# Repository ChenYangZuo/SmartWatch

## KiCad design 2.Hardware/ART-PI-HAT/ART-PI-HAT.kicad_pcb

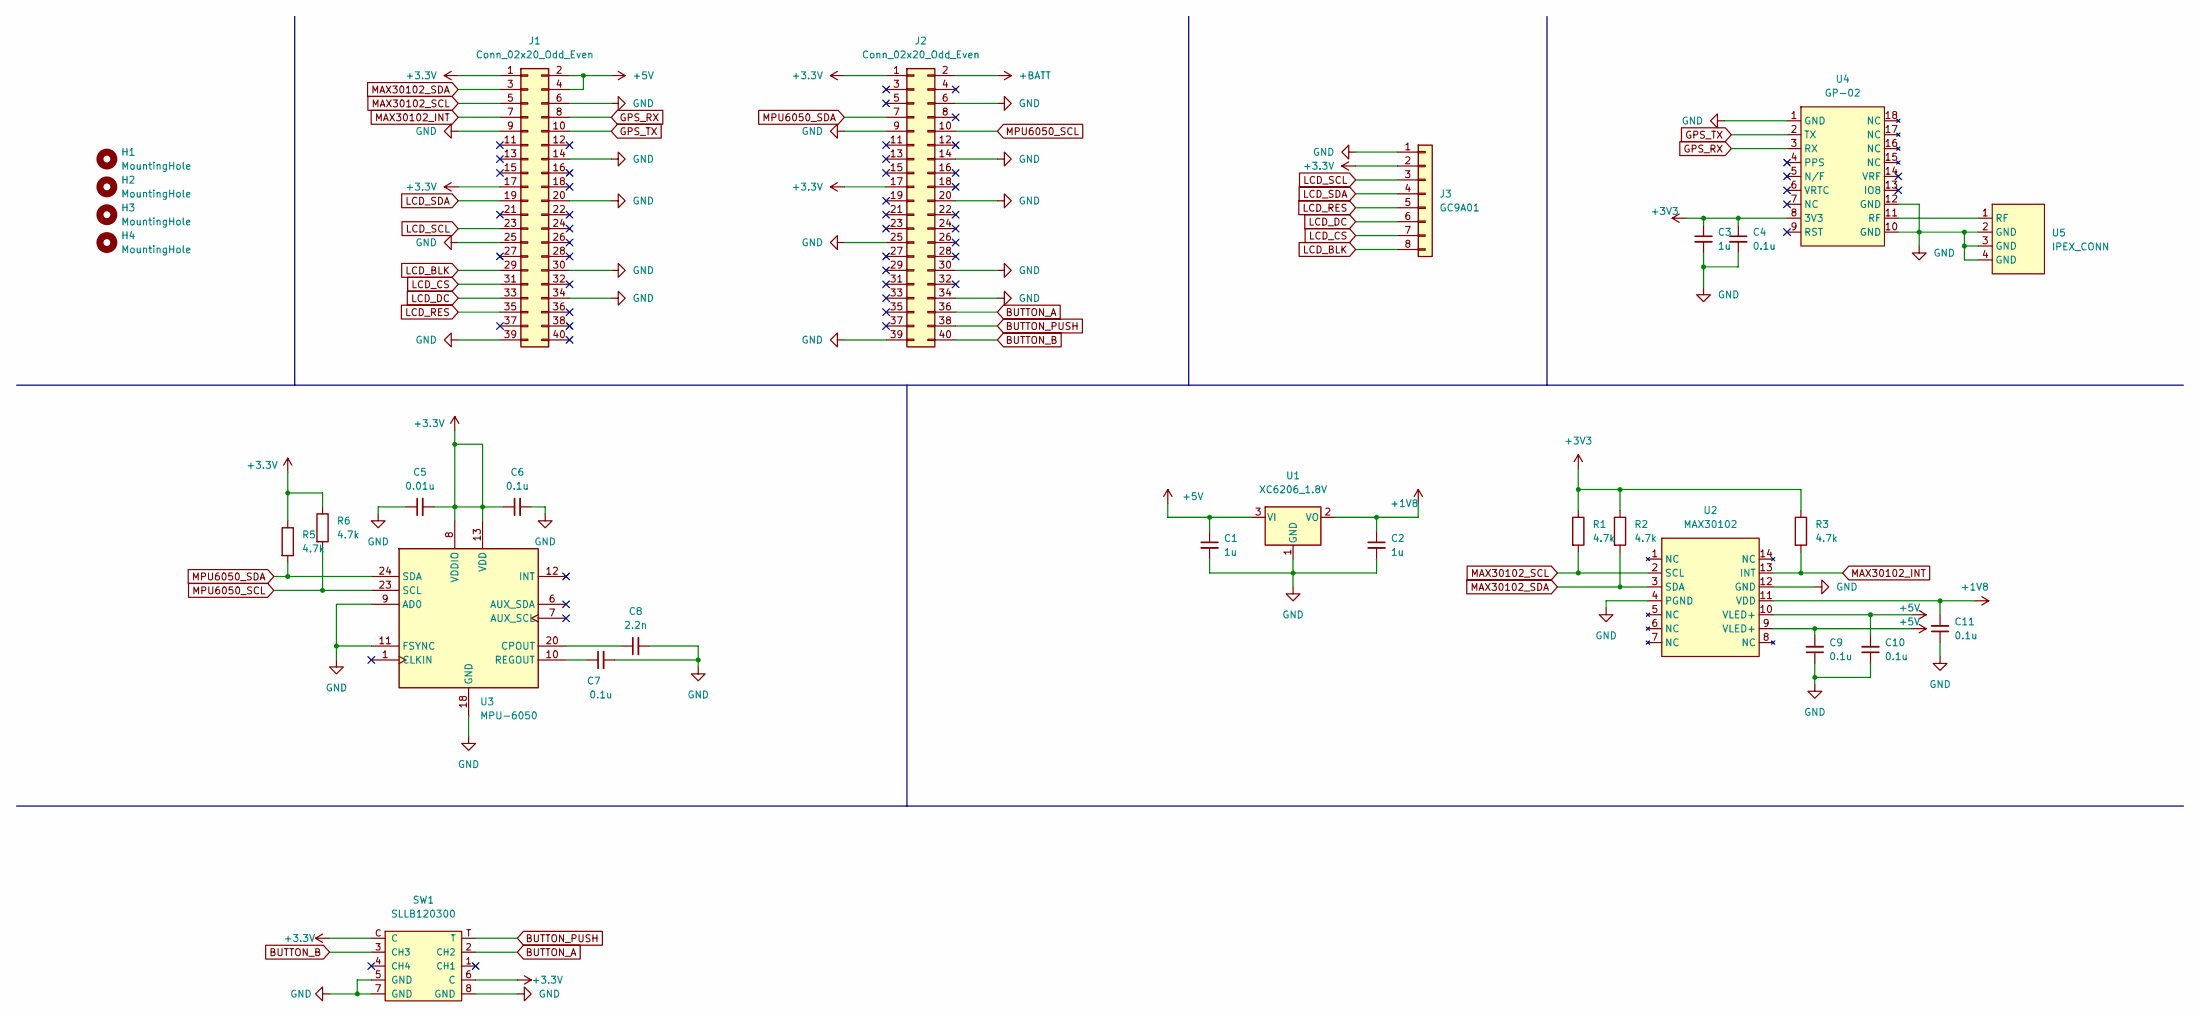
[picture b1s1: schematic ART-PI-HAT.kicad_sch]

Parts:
C1, C2, C3: 1u; C_0603_1608Metric
C4, C6, C7, C9, C10, C11: 0.1u; C_0603_1608Metric
C5: 0.01u; C_0603_1608Metric
C8: 2.2n; C_0603_1608Metric
H1, H2, H3, H4: MountingHole; TH_RASP_HAT
J1, J2: Conn_02x20_Odd_Even; PinHeader_2x20_P2.54mm_Vertical
J3: GC9A01; PinSocket_1x08_P2.54mm_Vertical
R1, R2, R3, R5, R6: 4.7k; R_0603_1608Metric
SW1: SLLB120300; SW-SMD_SLLB120200
U1: XC6206_1.8V; SOT-23
U2: MAX30102; Maxim_OLGA-14_3.3x5.6mm_P0.8mm
U3: MPU-6050; InvenSense_QFN-24_4x4mm_P0.5mm
U4: GP-02
U5: IPEX_CONN

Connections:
+1V8: C2.1, C11.2, U1.2 (VO), U2.11 (VDD)
+5V: C1.1, C9.2, C10.2, J1.2, J1.4, U1.3 (VI), U2.9 (VLED+), U2.10 (VLED+)
+BATT: J2.2
BUTTON_A: J2.36, SW1.2 (CH2)
BUTTON_B: J2.40, SW1.3 (CH3)
BUTTON_PUSH: J2.38, SW1.T
GND: C1.2, C2.2, C3.2, C4.2, C5.1, C6.2, C7.2, C8.2, C9.1, C10.1, C11.1, J1.6, J1.9, J1.14, J1.20, J1.25, J1.30, J1.34, J1.39, J2.6, J2.9, J2.14, J2.20, J2.25, J2.30, J2.34, J2.39, J3.1, SW1.5 (GND), SW1.7 (GND), SW1.8 (GND), U1.1 (GND), U2.4 (PGND), U2.12 (GND), U3.9 (AD0), U3.11 (FSYNC), U3.18 (GND), U4.1 (GND), U4.10 (GND), U4.12 (GND), U5.2 (GND), U5.3 (GND), U5.4 (GND)
GPS_RX: J1.8, U4.3 (RX)
GPS_TX: J1.10, U4.2 (TX)
LCD_BLK: J1.29, J3.8
LCD_CS: J1.31, J3.7
LCD_DC: J1.33, J3.6
LCD_RES: J1.35, J3.5
LCD_SCL: J1.23, J3.3
LCD_SDA: J1.19, J3.4
MAX30102_INT: J1.7, R3.2, U2.13 (INT)
MAX30102_SCL: J1.5, R1.2, U2.2 (SCL)
MAX30102_SDA: J1.3, R2.2, U2.3 (SDA)
MPU6050_SCL: J2.10, R6.2, U3.23 (SCL)
MPU6050_SDA: J2.7, R5.2, U3.24 (SDA)
unnamed: C7.1, U3.10 (REGOUT)
unnamed: C8.1, U3.20 (CPOUT)
unnamed: U4.11 (RF), U5.1 (RF)

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
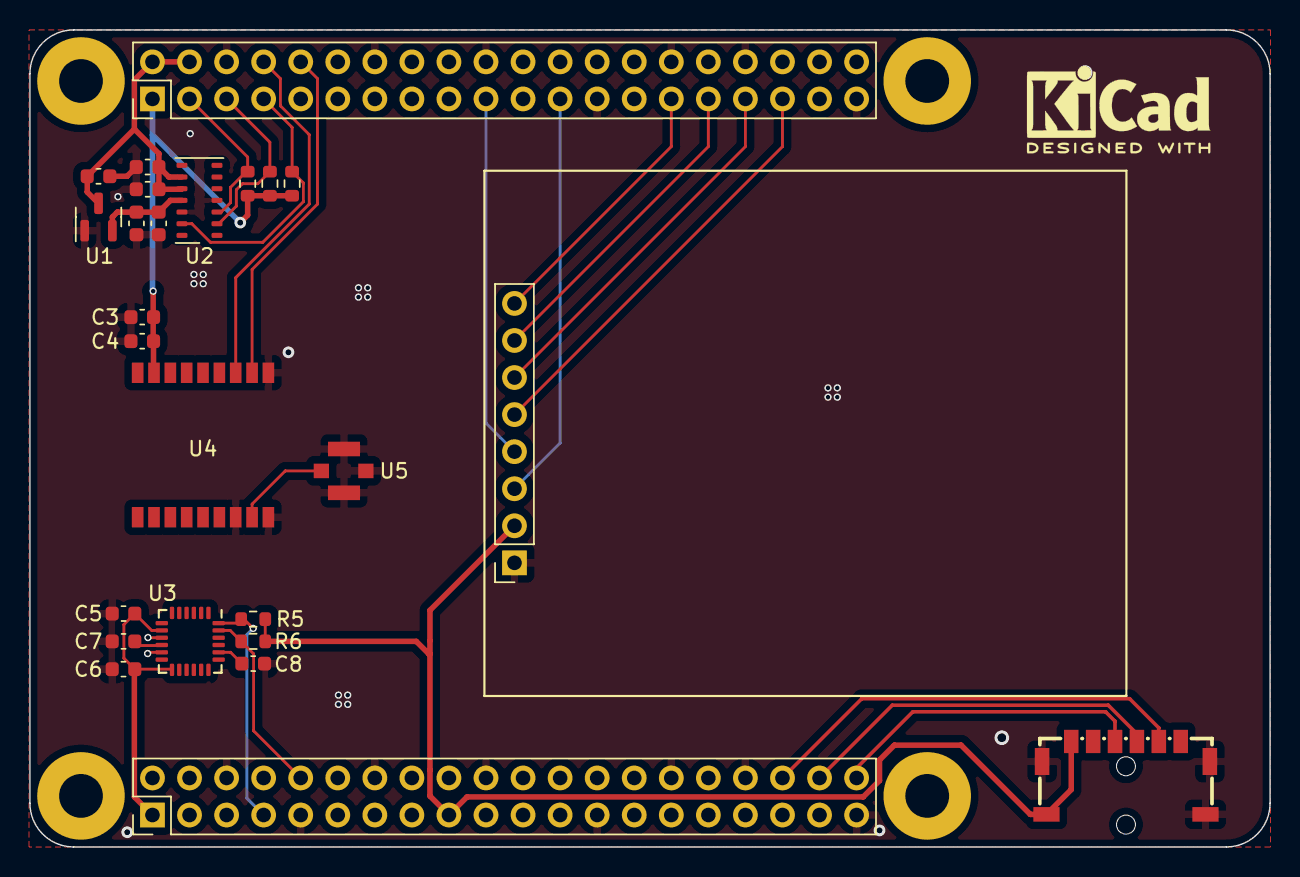
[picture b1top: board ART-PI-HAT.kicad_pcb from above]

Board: 2 copper layers, 85.0 x 56.0 mm, 29 parts (0 on the bottom side), 23 nets.

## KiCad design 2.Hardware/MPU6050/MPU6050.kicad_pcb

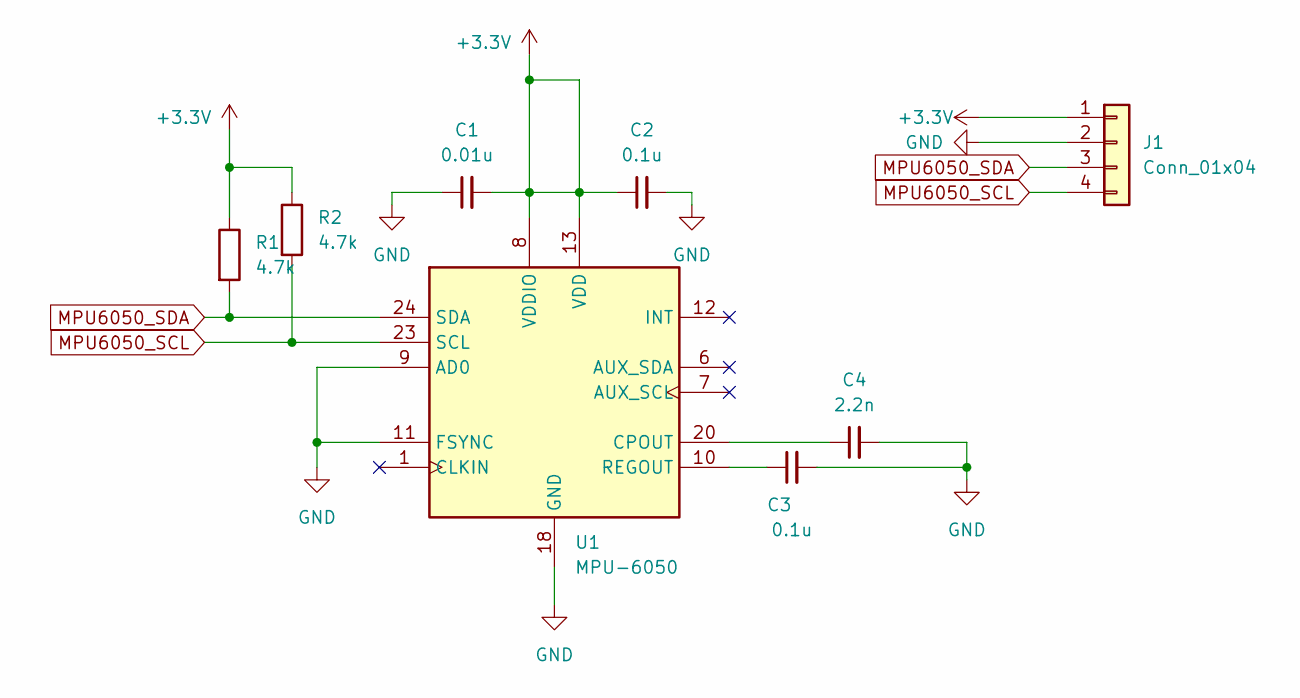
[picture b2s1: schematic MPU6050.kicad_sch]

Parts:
C1: 0.01u; C_0603_1608Metric
C2, C3: 0.1u; C_0603_1608Metric
C4: 2.2n; C_0603_1608Metric
J1: Conn_01x04; PinHeader_1x04_P2.54mm_Vertical
R1, R2: 4.7k; R_0603_1608Metric
U1: MPU-6050; InvenSense_QFN-24_4x4mm_P0.5mm

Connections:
+3V3: C1.2, C2.1, J1.1, R1.1, R2.1, U1.8 (VDDIO), U1.13 (VDD)
GND: C1.1, C2.2, C3.2, C4.2, J1.2, U1.9 (AD0), U1.11 (FSYNC), U1.18 (GND)
MPU6050_SCL: J1.4, R2.2, U1.23 (SCL)
MPU6050_SDA: J1.3, R1.2, U1.24 (SDA)
unnamed: C3.1, U1.10 (REGOUT)
unnamed: C4.1, U1.20 (CPOUT)

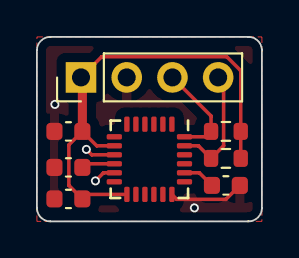
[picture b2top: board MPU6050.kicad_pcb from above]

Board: 2 copper layers, 12.5 x 10.2 mm, 8 parts (0 on the bottom side), 6 nets.

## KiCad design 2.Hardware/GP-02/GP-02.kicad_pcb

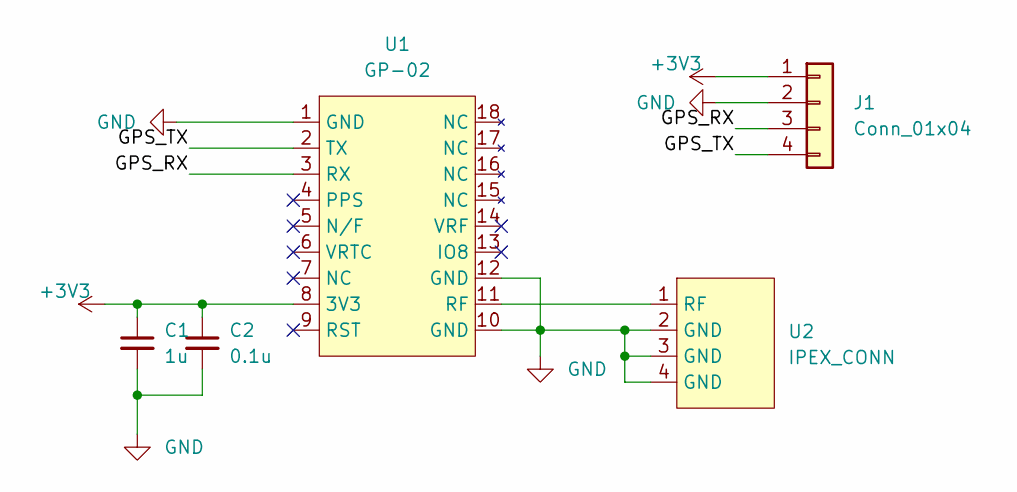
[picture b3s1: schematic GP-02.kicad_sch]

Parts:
C1: 1u; C_0603_1608Metric
C2: 0.1u; C_0603_1608Metric
J1: Conn_01x04; PinHeader_1x04_P2.54mm_Vertical
U1: GP-02
U2: IPEX_CONN

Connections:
+3V3: C1.1, C2.1, J1.1, U1.8 (3V3)
/GPS_RX: J1.3, U1.3 (RX)
/GPS_TX: J1.4, U1.2 (TX)
GND: C1.2, C2.2, J1.2, U1.1 (GND), U1.10 (GND), U1.12 (GND), U2.2 (GND), U2.3 (GND), U2.4 (GND)
unnamed: U1.11 (RF), U2.1 (RF)

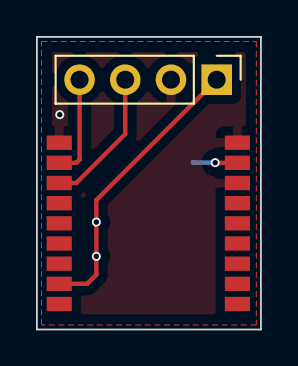
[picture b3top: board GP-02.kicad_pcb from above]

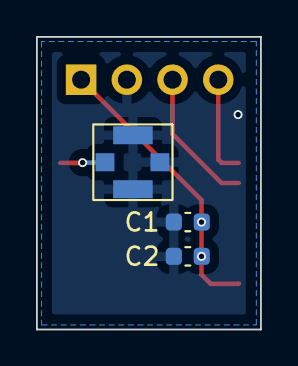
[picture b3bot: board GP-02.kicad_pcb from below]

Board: 2 copper layers, 12.4 x 16.3 mm, 5 parts (3 on the bottom side), 5 nets.

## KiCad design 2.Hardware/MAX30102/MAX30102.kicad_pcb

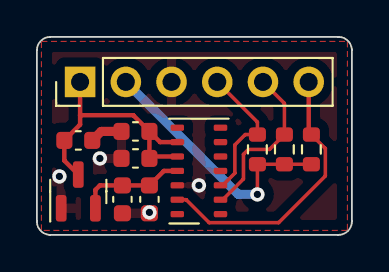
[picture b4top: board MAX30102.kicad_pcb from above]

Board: 2 copper layers, 17.5 x 11.0 mm, 11 parts (0 on the bottom side), 7 nets.

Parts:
C1, C2: 1u; C_0603_1608Metric
C3, C4, C5: 0.1u; C_0603_1608Metric
J1: Conn_01x06; PinHeader_1x06_P2.54mm_Vertical
R1, R2, R4: 4.7k; R_0603_1608Metric
U1: XC6206_1.8V; SOT-23
U2: MAX30102; Maxim_OLGA-14_3.3x5.6mm_P0.8mm

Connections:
+1V8: C2.1, C5.2, U1.2 (VO), U2.11 (VDD)
+3V3: J1.2, R1.1, R2.1, R4.1
+5V: C1.1, C3.2, C4.2, J1.1, U1.3 (VI), U2.9 (VLED+), U2.10 (VLED+)
/MAX30102_INT: J1.6, R4.2, U2.13 (INT)
/MAX30102_SCL: J1.5, R1.2, U2.2 (SCL)
/MAX30102_SDA: J1.4, R2.2, U2.3 (SDA)
GND: C1.2, C2.2, C3.1, C4.1, C5.1, J1.3, U1.1 (GND), U2.4 (PGND), U2.12 (GND)

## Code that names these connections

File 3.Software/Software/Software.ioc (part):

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Mcu.Name=STM32H750XBHx
Mcu.Package=TFBGA240
Mcu.UserName=STM32H750XBHx
PA0.Mode=Asynchronous
PA0.Signal=UART4_TX
PA10.Mode=Asynchronous
PA10.Signal=USART1_RX
PA13\ (JTMS/SWDIO).Mode=Serial_Wire
PA13\ (JTMS/SWDIO).Signal=DEBUG_JTMS-SWDIO
PA14\ (JTCK/SWCLK).Mode=Serial_Wire
PA14\ (JTCK/SWCLK).Signal=DEBUG_JTCK-SWCLK
PA8.GPIOParameters=GPIO_Label,GPIO_ModeDefaultEXTI
PA8.GPIO_Label=MAX30102_INT
PA8.GPIO_ModeDefaultEXTI=GPIO_MODE_IT_FALLING
PA8.Signal=GPXTI8
PA9.Mode=Asynchronous
PA9.Signal=USART1_TX
PB0.GPIOParameters=GPIO_Label
PB0.GPIO_Label=BUTTON_PUSH
PB0.Signal=GPIO_Input
PB13.GPIOParameters=GPIO_Speed,PinState,GPIO_PuPd,GPIO_Label
PB13.GPIO_Label=LCD_CS
PB13.GPIO_PuPd=GPIO_PULLUP
PB13.GPIO_Speed=GPIO_SPEED_FREQ_HIGH
PB13.PinState=GPIO_PIN_SET
PB13.Signal=GPIO_Output
PB2.GPIOParameters=GPIO_Label
PB2.GPIO_Label=BUTTON_B
PB2.Signal=GPIO_Input
PB8.Mode=I2C
PB8.Signal=I2C1_SCL
PB9.Mode=I2C
PB9.Signal=I2C1_SDA
PC14-OSC32_IN\ (OSC32_IN).Mode=LSE-External-Oscillator
PC14-OSC32_IN\ (OSC32_IN).Signal=RCC_OSC32_IN
PC15-OSC32_OUT\ (OSC32_OUT).Mode=LSE-External-Oscillator
PC15-OSC32_OUT\ (OSC32_OUT).Signal=RCC_OSC32_OUT
PG14.GPIOParameters=GPIO_Label
PG14.GPIO_Label=MPU6050_INT
PG14.Signal=GPIO_Input
PH0-OSC_IN\ (PH0).Mode=HSE-External-Oscillator
PH0-OSC_IN\ (PH0).Signal=RCC_OSC_IN
PH1-OSC_OUT\ (PH1).Mode=HSE-External-Oscillator
PH1-OSC_OUT\ (PH1).Signal=RCC_OSC_OUT
PH11.Mode=I2C
PH11.Signal=I2C4_SCL
PH12.Mode=I2C
PH12.Signal=I2C4_SDA
PH3.GPIOParameters=GPIO_Label
PH3.GPIO_Label=BUTTON_A
PH3.Signal=GPIO_Input
PH7.GPIOParameters=GPIO_Speed,PinState,GPIO_PuPd,GPIO_Label
PH7.GPIO_Label=LCD_RES
PH7.GPIO_PuPd=GPIO_PULLUP
PH7.GPIO_Speed=GPIO_SPEED_FREQ_HIGH
PH7.PinState=GPIO_PIN_SET
PH7.Signal=GPIO_Output
PH9.GPIOParameters=GPIO_Speed,PinState,GPIO_PuPd,GPIO_Label
PH9.GPIO_Label=LCD_DC
PH9.GPIO_PuPd=GPIO_PULLUP
PH9.GPIO_Speed=GPIO_SPEED_FREQ_HIGH
PH9.PinState=GPIO_PIN_SET
PH9.Signal=GPIO_Output
PI1.Mode=Full_Duplex_Master
PI1.Signal=SPI2_SCK
PI2.Mode=Full_Duplex_Master
PI2.Signal=SPI2_MISO
PI3.Mode=Full_Duplex_Master
PI3.Signal=SPI2_MOSI
PI7.GPIOParameters=GPIO_Speed,PinState,GPIO_PuPd,GPIO_Label
PI7.GPIO_Label=LCD_BLK
PI7.GPIO_PuPd=GPIO_PULLUP
PI7.GPIO_Speed=GPIO_SPEED_FREQ_HIGH
PI7.PinState=GPIO_PIN_SET
PI7.Signal=GPIO_Output
PI8.GPIOParameters=GPIO_Label
PI8.GPIO_Label=LED
PI8.Signal=GPIO_Output
PI9.Mode=Asynchronous
PI9.Signal=UART4_RX
RCC.HSE_VALUE=25000000
RCC.SYSCLKFreq_VALUE=480000000
RCC.SYSCLKSource=RCC_SYSCLKSOURCE_PLLCLK
board=custom

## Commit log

2022-01-19 add images.
2022-01-21 add lever switch.
2022-01-22 update images.
